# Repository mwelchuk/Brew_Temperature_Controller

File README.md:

# Brew Temperature Controller

This project is a small heater controller that I have made to enable a few spare 3D printer parts I had lying arround to be used to control the temperature of my beer when brewing. I had been using a full RAMPS1.4 controller with a 4 line display, but this was very bulky. Rather than the Arduino Mega utilised with the RAMPS board, this uses an Arduino Uno, which is much smaller.

The device is fully powered from the PSU that's needed to supply power to the heater (this can not be pulled from the Arduino). If plugged in via USB, the set temperature, power output (scaled from 0-255) and current temperature are logged approximately once a second.

## PCB Ideas

- Improve layout of MOSFET now a more powerful transistor is being used.
- Getting noise back in (cheap) power supply, better smoothing?

## Code Ideas

- Better PID library

## Parts

- Parts below from CPC (cpc.farnell.com):

```
Order Code	Qty	Manufacturer Part Number	Manufacturer / Description									Line Price Ex. VAT (Inc. Vat)
SW02467		2	MCDTS6-1R			MULTICOMP PRO  Switch, Tactile 4.3mm 260g							0.22
CN21011		1	CTBP9358/4			CAMDENBOSS  5.08mm Horizontal Pluggable Terminal Block Header, 4-Pole, 15A			0.43
CN19453		1	CTB0708/2			CAMDENBOSS  PCB Terminal, High Power, 5.08mm, 2 Way						0.49
FF02092		2	MCCQ-122			MULTICOMP PRO  Fuseholder, PCB Mount, Mini Blade						0.48
CA08185		1	MCMR50V106M5X7			MULTICOMP PRO  Electrolytic Capacitor, 10 µF, 50 V, MCMR Series, ± 20%, Radial Leaded, 5 mm	0.05
SC11131		1	STP60NF06L			STMICROELECTRONICS  Power MOSFET, N Channel, 60 V, 60 A, 0.014 ohm, TO-220, Through Hole	1.36
```

- Nokia 5110 style screen with the following pinout:

```
Pin	Use
1	RST
2	CE
3	DC
4	DIN
5	CLK
6	VCC
7	LIGHT
8	GND
```

- Arduino Uno, cheap clone used
- Fuses: Standard Car mini Fuses. Used 5A (smallest I had) for electronics, 20A for heater output.
- Heater I found a standard 22cm circular 3D printer heated bed fits nicely under my brew bucket (it was this that inspired the build).
- Thermistor: Standard 100K thermistor, as used on many 3D printers.
- PSU: Currently using spare 0.8A 12v PSU as might be used on a small 3D printer.

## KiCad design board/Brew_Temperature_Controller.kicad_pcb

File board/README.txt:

Brew Temperature Controller
===========================

Ideas for v.2
-------------

- Add LED to show when heater is on
- More powerful MOSFET

Code
----

- https://www.youtube.com/watch?v=t31n6Y-0bYg
  - Look at U8glib: https://github.com/olikraus/u8glib

Parts
----

Parts below from cpc.farnell.com:

Order Code	Qty	Manufacturer Part Number	Manufacturer / Description									Line Price Ex. VAT (Inc. Vat)
SW02467		10	MCDTS6-1R			MULTICOMP PRO  Switch, Tactile 4.3mm 260g							0.9
CN21011		5	CTBP9358/4			CAMDENBOSS  5.08mm Horizontal Pluggable Terminal Block Header, 4-Pole, 15A			1.8
CN19453		5	CTB0708/2			CAMDENBOSS  PCB Terminal, High Power, 5.08mm, 2 Way						2.05
FF02092		10	MCCQ-122			MULTICOMP PRO  Fuseholder, PCB Mount, Mini Blade						1.8
CA08185		5	MCMR50V106M5X7			MULTICOMP PRO  Electrolytic Capacitor, 10 µF, 50 V, MCMR Series, ± 20%, Radial Leaded, 5 mm	0.2
SC11074		5	IRLU024NPBF			INFINEON  Power MOSFET, N Channel, 55 V, 17 A, 0.065 ohm, TO-251AA, Through Hole		2.4

- Need Nokia 5110 style screen

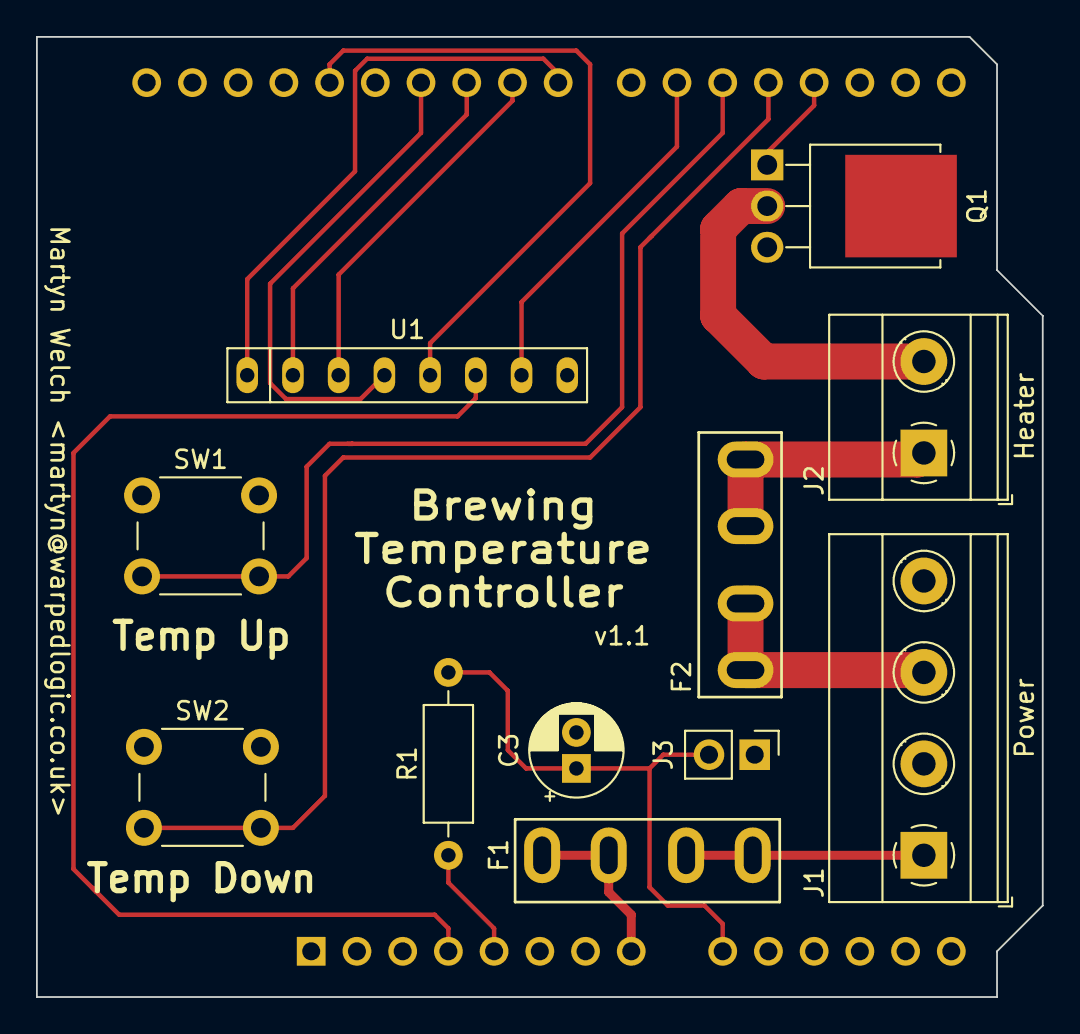
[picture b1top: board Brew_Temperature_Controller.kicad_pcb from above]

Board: 2 copper layers, 55.9 x 53.3 mm, 12 parts (1 on the bottom side), 18 nets.

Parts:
A1: Arduino_UNO_R3
C3: 10uF; CP_Radial_D5.0mm_P2.00mm
F1, F2: MCCQ-122
J1: CTBP9358/4; TerminalBlock_Phoenix_MKDS-1,5-4-5.08_1x04_P5.08mm_Horizont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
J2: CTB0708/2; TerminalBlock_Phoenix_MKDS-1,5-2-5.08_1x02_P5.08mm_Horizont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
J3: Conn_01x02_Male; PinHeader_1x02_P2.54mm_Vertical
Q1: IRLU024NPBF; TO-251-3-1EP_Horizontal_TabDown
R1: 4K7; R_Axial_DIN0207_L6.3mm_D2.5mm_P10.16mm_Horizontal
SW1, SW2: MCDTS6-1R; SW_PUSH_6mm_H4.3mm
U1: Nokia_5110_Module

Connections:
+3V3: A1.4, U1.6
+5V: A1.5, R1.1
+12V: A1.8, F1.1
Button1: A1.20, SW1.2
Button2: A1.19, SW2.2
CE: A1.25, U1.2
DC: A1.24, U1.3
GND: A1.6, A1.7, A1.29, C3.2, J1.2, J1.4, J3.1, Q1.3, SW1.1, SW2.1, U1.8
HEATER: A1.18, Q1.1
LIGHT: A1.21, U1.7
unnamed: F1.2, J1.1
unnamed: F2.2, J1.3
unnamed: J2.2, Q1.2
RST: A1.23, U1.1
SCLK: A1.28, U1.5
SDIN: A1.26, U1.4
THERM: A1.9, C3.1, J3.2, R1.2
Vdrive: F2.1, J2.1

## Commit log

2020-07-25 Initial code start at code implementation
    This code is not complete, but a first test state:
    - Screen working and layout almost complete
    - Temp set point buttons function (still needs limits)
    - Temperature sensor working
    - Integration of PID loop underway
2020-07-25 Board tweaks and software update
    The use of D2 to control the heater was a mistake as it does not
    provide PWM, switch to using D3.
    The chosen MOSFET was not suitable for driving the heater at full
    current and has thus been switched for a more powerful one.
    Move the README so that it's more general for the whole project rather
    than just the board design and use Markdown.
2020-07-25 Add image of controller
    Add an image of the controller to the README.md.
